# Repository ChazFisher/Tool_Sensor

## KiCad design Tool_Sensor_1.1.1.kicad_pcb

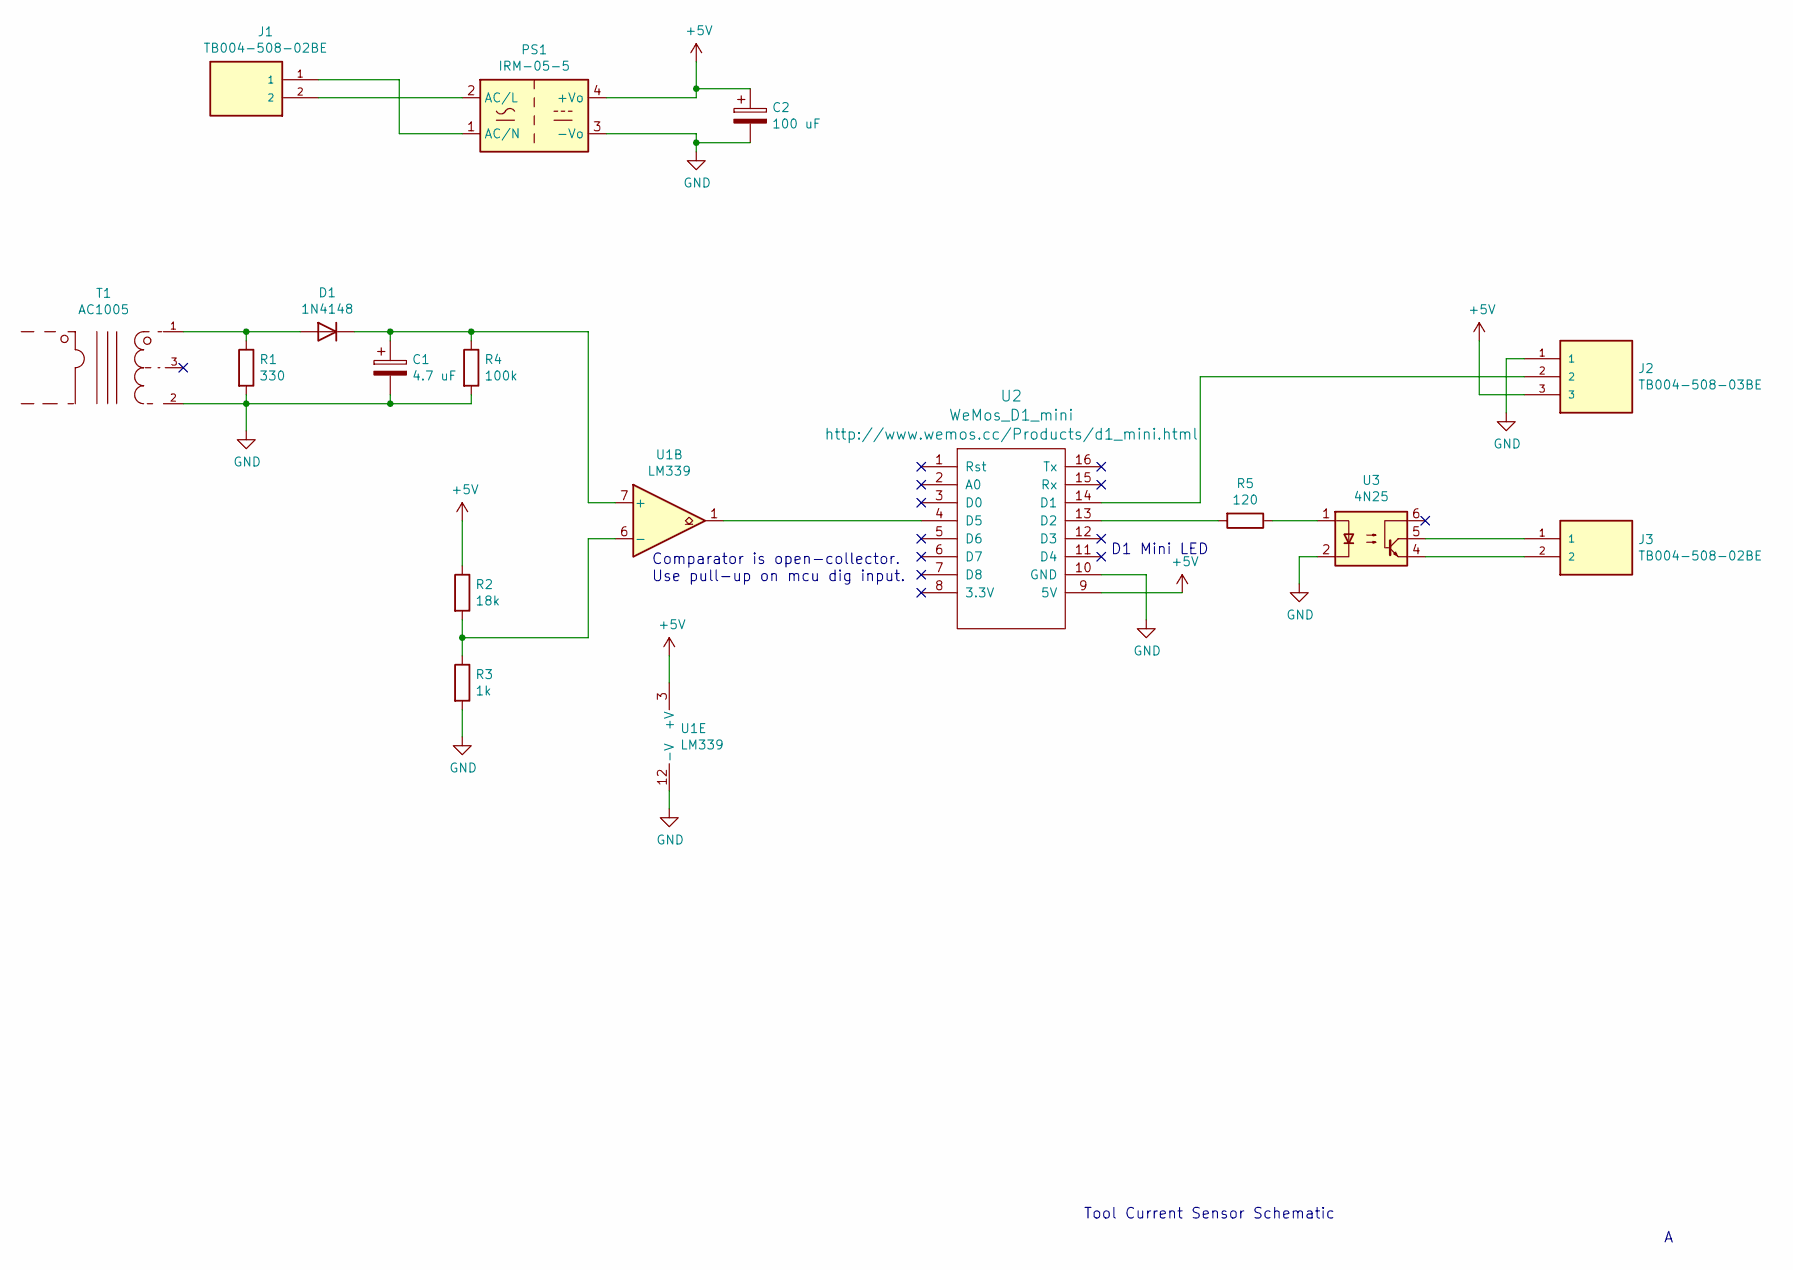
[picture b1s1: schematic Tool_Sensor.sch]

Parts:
C1: 4.7 uF; CP_Radial_D6.3mm_P2.50mm
C2: 100 uF; CP_Radial_D8.0mm_P5.00mm
D1: 1N4148; D_DO-35_SOD27_P12.70mm_Horizontal
J1, J3: TB004-508-02BE; CUI_TB004-508-02BE
J2: TB004-508-03BE; CUI_TB004-508-03BE
PS1: IRM-05-5; Converter_ACDC_MeanWell_IRM-05-xx_THT
R1: 330; R_Axial_DIN0309_L9.0mm_D3.2mm_P12.70mm_Horizontal
R2: 18k; R_Axial_DIN0309_L9.0mm_D3.2mm_P12.70mm_Horizontal
R3: 1k; R_Axial_DIN0309_L9.0mm_D3.2mm_P12.70mm_Horizontal
R4: 100k; R_Axial_DIN0309_L9.0mm_D3.2mm_P12.70mm_Horizontal
R5: 120; R_Axial_DIN0309_L9.0mm_D3.2mm_P12.70mm_Horizontal
T1: AC1005; Talema_Group_LLC-AC1005-0-0-MFG; digikey description CURR SENSE XFMR 40A T/H
U1: LM339; DIP-14_W7.62mm
U2: WeMos_D1_mini; wemos-d1-mini-connectors-only
U3: 4N25; DIP-6_W7.62mm

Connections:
+5V: C2.1, J2.3, PS1.4 (+Vo), R2.1, U1.3 (+V), U2.9 (5V)
GND: C1.2, C2.2, J2.1, PS1.3 (-Vo), R1.2, R3.2, R4.2, T1.2, U1.12 (-V), U2.10 (GND), U3.2
unnamed: C1.1, D1.1 (K), R4.1, U1.7 (+)
unnamed: D1.2 (A), R1.1, T1.1
unnamed: J1.1, PS1.1 (AC/N)
unnamed: J1.2, PS1.2 (AC/L)
unnamed: J2.2, U2.14 (D1)
unnamed: J3.1, U3.5
unnamed: J3.2, U3.4
unnamed: R2.2, R3.1, U1.6 (-)
unnamed: R5.1, U3.1
unnamed: R5.2, U2.13 (D2)
unnamed: U1.1, U2.4 (D5)

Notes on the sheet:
Tool Current Sensor Schematic
Comparator is open-collector. Use pull-up on mcu dig input.
D1 Mini LED

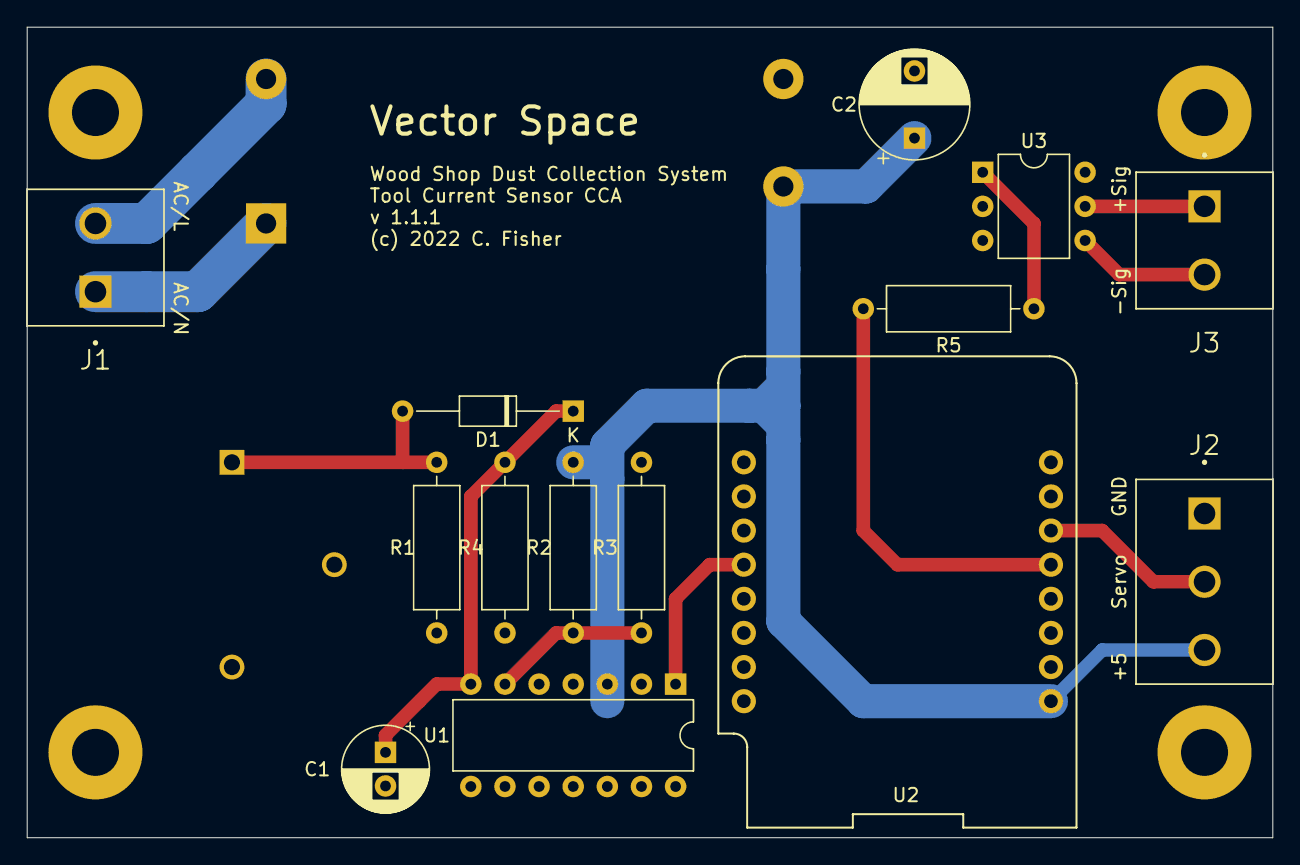
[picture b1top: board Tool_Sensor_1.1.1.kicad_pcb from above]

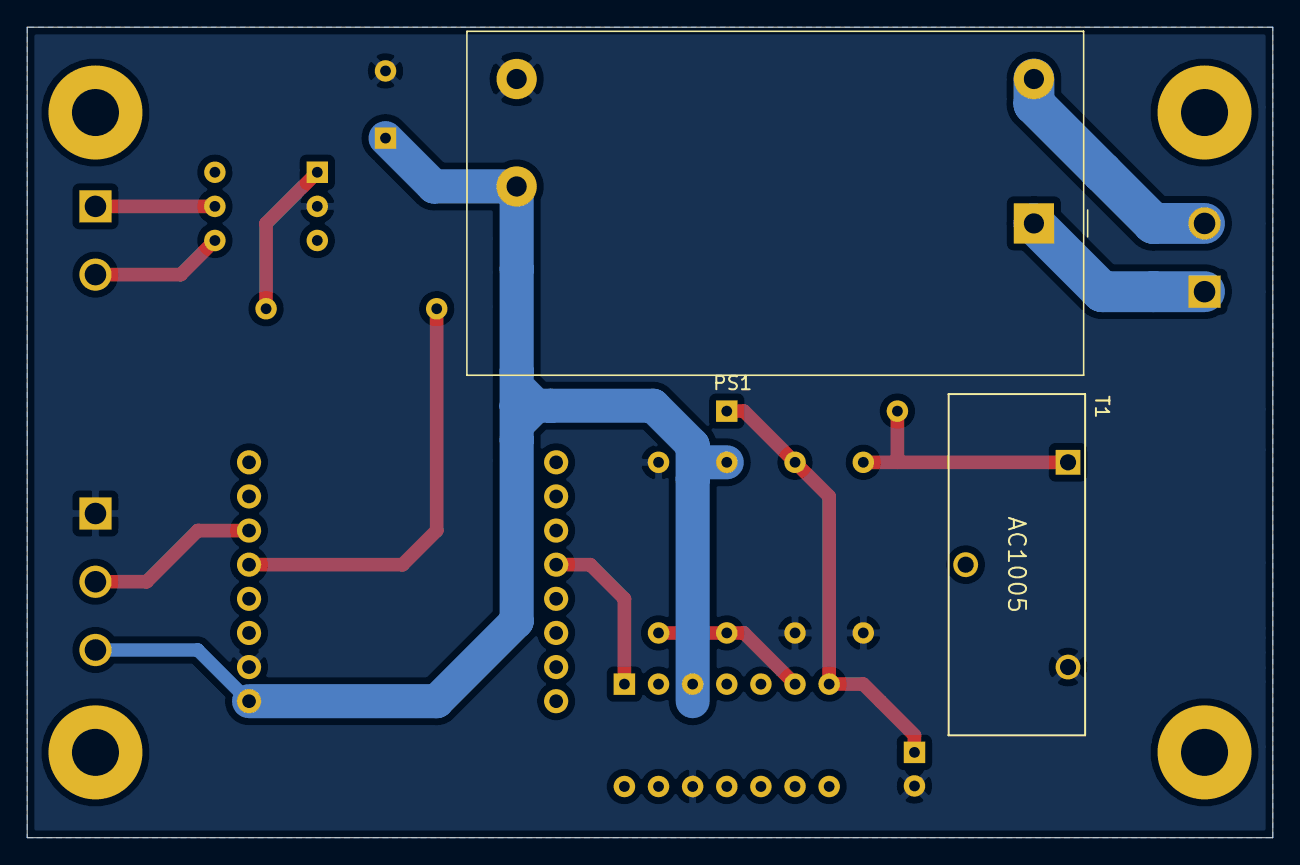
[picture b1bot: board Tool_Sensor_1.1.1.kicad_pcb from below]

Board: 2 copper layers, 92.7 x 60.3 mm, 16 parts (2 on the bottom side), 13 nets.

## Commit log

2023-09-24 Initial hardware version deployed at Memorial Ave.

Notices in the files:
Tool_Sensor_1.1.1.kicad_pcb:
(c) 2022 C. Fisher
